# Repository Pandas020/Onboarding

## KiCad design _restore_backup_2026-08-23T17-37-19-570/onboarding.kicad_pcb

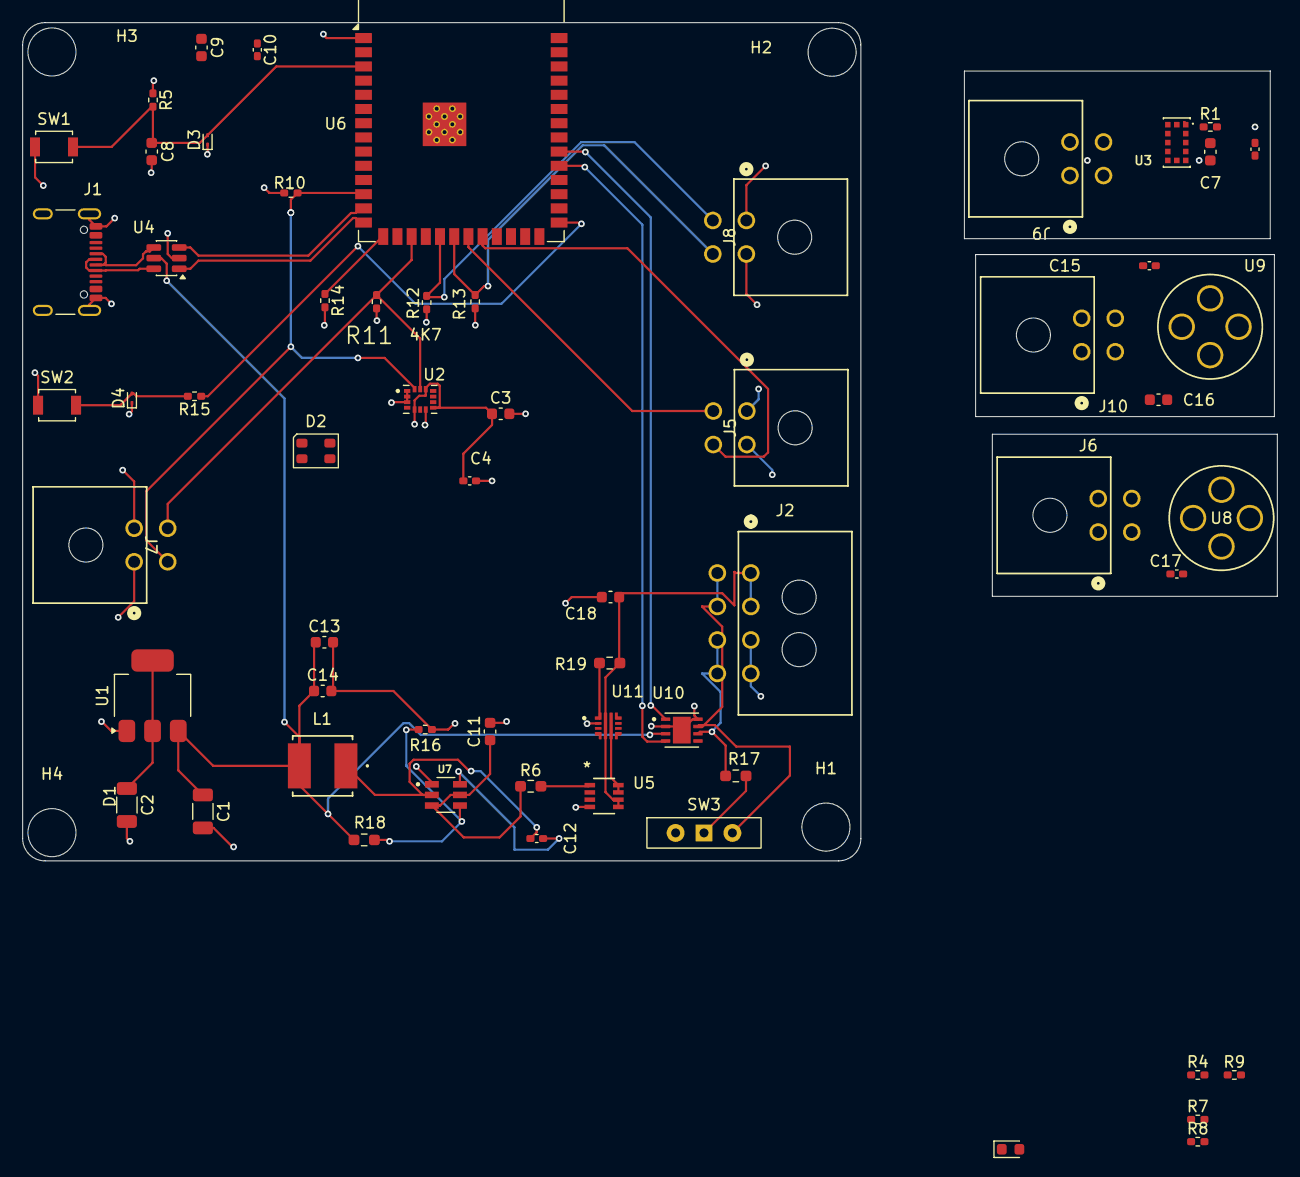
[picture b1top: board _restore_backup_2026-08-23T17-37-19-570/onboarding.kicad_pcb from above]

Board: 4 copper layers, 112.3 x 75.0 mm, 65 parts (0 on the bottom side), 39 nets.

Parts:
C1, C2: 22uF; C_1206_3216Metric
C3: 1uF; C_0603_1608Metric
C4, C5, C10, C12, C15, C17: 100nF; C_0402_1005Metric_Pad0.74x0.62mm_HandSolder
C7, C11: 4U7; C_0603_1608Metric
C8: 1u; C_0603_1608Metric
C9, C13, C14, C16, C18: 10uF; C_0603_1608Metric
D1: RED; LED_0603_1608Metric
D2: CLV1L-FKB; LED_Cree-PLCC4_3.2x2.8mm_CCW
D3, D4: ESD3.3; D_SOD-923
H1, H2, H3, H4: MountingHole; MountingHole_4.3mm_M4
J1: USB_C_Receptacle_USB2.0_16P; USB_C_Receptacle_GCT_USB4105-xx-A_16P_TopMnt_Horizontal
J2: 430450800; CONN_SD-43045-001_08_MOL
J5, J6, J7, J8, J9, J10: 430450400; CONN_SD-43045-001_04_MOL
L1: NRS5030T3R3MMGJ; IND_NRS5030T3R3MMGJ_TAY-M
R1, R5, R15: 10K; R_0402_1005Metric_Pad0.72x0.64mm_HandSolder
R4, R7, R8, R9, R14: 1K; R_0402_1005Metric_Pad0.72x0.64mm_HandSolder
R6, R17: 100R; R_0603_1608Metric_Pad0.98x0.95mm_HandSolder
R10, R11, R12, R13: 4K7; R_0402_1005Metric_Pad0.72x0.64mm_HandSolder
R16: 13K7; R_0402_1005Metric_Pad0.72x0.64mm_HandSolder
R18: 100K; R_0603_1608Metric_Pad0.98x0.95mm_HandSolder
R19: 470K; R_0603_1608Metric_Pad0.98x0.95mm_HandSolder
SW1: RESET; SW_SPST_B3U-1000P
SW2: BOOT; SW_SPST_B3U-1000P
SW3: SW_Wuerth_450301014042; SW_Slide-03_Wuerth-WS-SLTV_10x2.5x6.4_P2.54mm
U1: LM1117DT-3.3; SOT-223-3_TabPin2
U2: ASM330LHHXTR; XDCR_ASM330LHHXTR
U3: VL53L0CXV0DH_1; XDCR_VL53L0CXV0DH_1
U4: USBLC6-2SC6; SOT-23-6
U5: STEF12SAGR; IC8_STEF12SAGR_STM
U6: ESP32-S3-WROOM-1
U7: LMR51420YFDDCR; SOT95P280X110-6N
U8: MLX90614ESF-BCF-000-TU; MLX90614xCF_MEL
U9: MLX90641ESF-BCB-000-TU; MLX90614xCF_MEL
U10: TJA1462ATK_0Z; SON65P300X300X100-9N
U11: LM73100RPWR; IC_LM73100RPWR

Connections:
+3V3: C2.1, C3.1, C4.1, C5.1, C7.1, C9.1, C10.1, C15.1, C16.1, C17.1, D2.1 (A), J5.1, J6.1, J7.1, J8.1, J9.1, J10.1, R1.1, R4.1, R5.1, R10.1, R11.1, R12.1, R13.1, R14.2, U1.2 (VO), U2.5 (VDD_IO), U2.8 (VDD), U2.12 (CS), U3.1 (AVDDVCSEL), U3.1.1 (AVDDVCSEL), U3.11 (AVDD), U6.2 (3V3), U8.3 (VDD), U9.2 (VDD), U10.5 (VIO)
+5V: C1.1, C13.1, C14.1, L1.2, R18.2, U1.3 (VI), U4.5 (VBUS), U10.3 (VCC)
+12V: C11.1, C18.1, J2.1, J2.2, R6.1, R19.2, U5.5 (Source), U5.6 (Source), U7.3 (VIN), U7.5 (EN), U11.5 (IN)
/BRAKE_PWM: J5.4, J6.4, U6.22 (IO14), U8.2 (SDA/PWM)
/BRAKE_SCL: J5.3, J6.3, U6.21 (IO13), U8.1 (SCL/Vz)
/B_RGB: R9.2, U6.35 (IO42)
/CANH: J2.5, J2.6, SW3.3 (A), U10.7 (CANH)
/CANL: J2.7, J2.8, R17.1, U10.6 (CANL)
/D+: J1.A6 (D+), J1.B6 (D+), U4.6 (I/O1)
/D-: J1.A7 (D-), J1.B7 (D-), U4.4 (I/O2)
/ESP_EN: C8.1, D3.2 (A2), R5.2, SW1.2 (B), U6.3 (EN)
/ESP_IO0: R15.1, U6.27 (IO0)
/FDCAN_RX: U6.31 (IO38), U10.4 (RXD)
/FDCAN_TX: U6.32 (IO39), U10.1 (TXD)
/G_RGB: R8.2, U6.34 (IO41)
/IO4: U2.4 (INT1), U6.4 (IO4)
/IO5: U2.9 (INT2), U6.5 (IO5)
/R_RGB: R7.2, U6.33 (IO40)
/SCL: J7.4, J9.4, R11.2, U2.13 (SCL), U3.10 (SCL), U6.17 (IO9)
/SCL2_TTS: J8.3, J10.3, R12.2, U6.19 (IO11), U9.4 (SCL)
/SDA: J7.3, J9.3, R10.2, U2.14 (SDA), U3.9 (SDA), U6.12 (IO8)
/SDA2_TTS: J8.4, J10.4, R13.2, U6.20 (IO12), U9.1 (SDA)
/USB_D+: U4.1 (I/O1), U6.14 (USB_D+)
/USB_D-: U4.3 (I/O2), U6.13 (USB_D-)
GND: C1.2, C2.2, C3.2, C4.2, C5.2, C7.2, C8.2, C9.2, C10.2, C11.2, C13.2, C14.2, C15.2, C16.2, C17.2, C18.2, D1.1 (K), D3.1 (A1), D4.1 (A1), J1.A1 (GND), J1.A12 (GND), J1.B1 (GND), J1.B12 (GND), J1.SH (SHIELD), J2.3, J2.4, J5.2, J6.2, J7.2, J8.2, J9.2, J10.2, R16.1, SW1.1 (A), SW2.1 (A), U1.1 (GND), U2.1 (SDO/SA0), U2.2 (MSDA), U2.3 (MSCL), U2.7 (GND), U3.2 (AVSSVCSEL), U3.3 (GND), U3.4 (GND), U3.6 (GND), U3.12 (GND), U4.2 (GND), U5.4 (GND), U6.1 (GND), U6.40 (GND), U6.41 (GND), U7.1 (GND), U8.4 (VSS), U9.3 (GND), U10.2 (GND), U10.8 (STB), U10.9 (GND), U11.2 (OVLO), U11.8 (GND), U11.9 (IMON)
unnamed: D1.2 (A), R4.2
unnamed: D2.4 (BK), R9.1
unnamed: D2.3 (GK), R8.1
unnamed: D2.2 (RK), R7.1
unnamed: D4.2 (A2), R15.2, SW2.2 (B)
unnamed: R17.2, SW3.1 (B)
unnamed: R1.2, U3.5 (XSHUT)
unnamed: R6.2, U5.1 (ILim)
unnamed: R14.1, U6.15 (IO3)
unnamed: C12.1, U7.6 (CB)
unnamed: R16.2, R18.1, U7.4 (FB)
unnamed: C12.2, L1.1, U7.2 (SW)
unnamed: R19.1, U11.1 (EN/UVLO)
unnamed: U5.7 (Vcc), U5.8 (Vcc), U11.6 (OUT)

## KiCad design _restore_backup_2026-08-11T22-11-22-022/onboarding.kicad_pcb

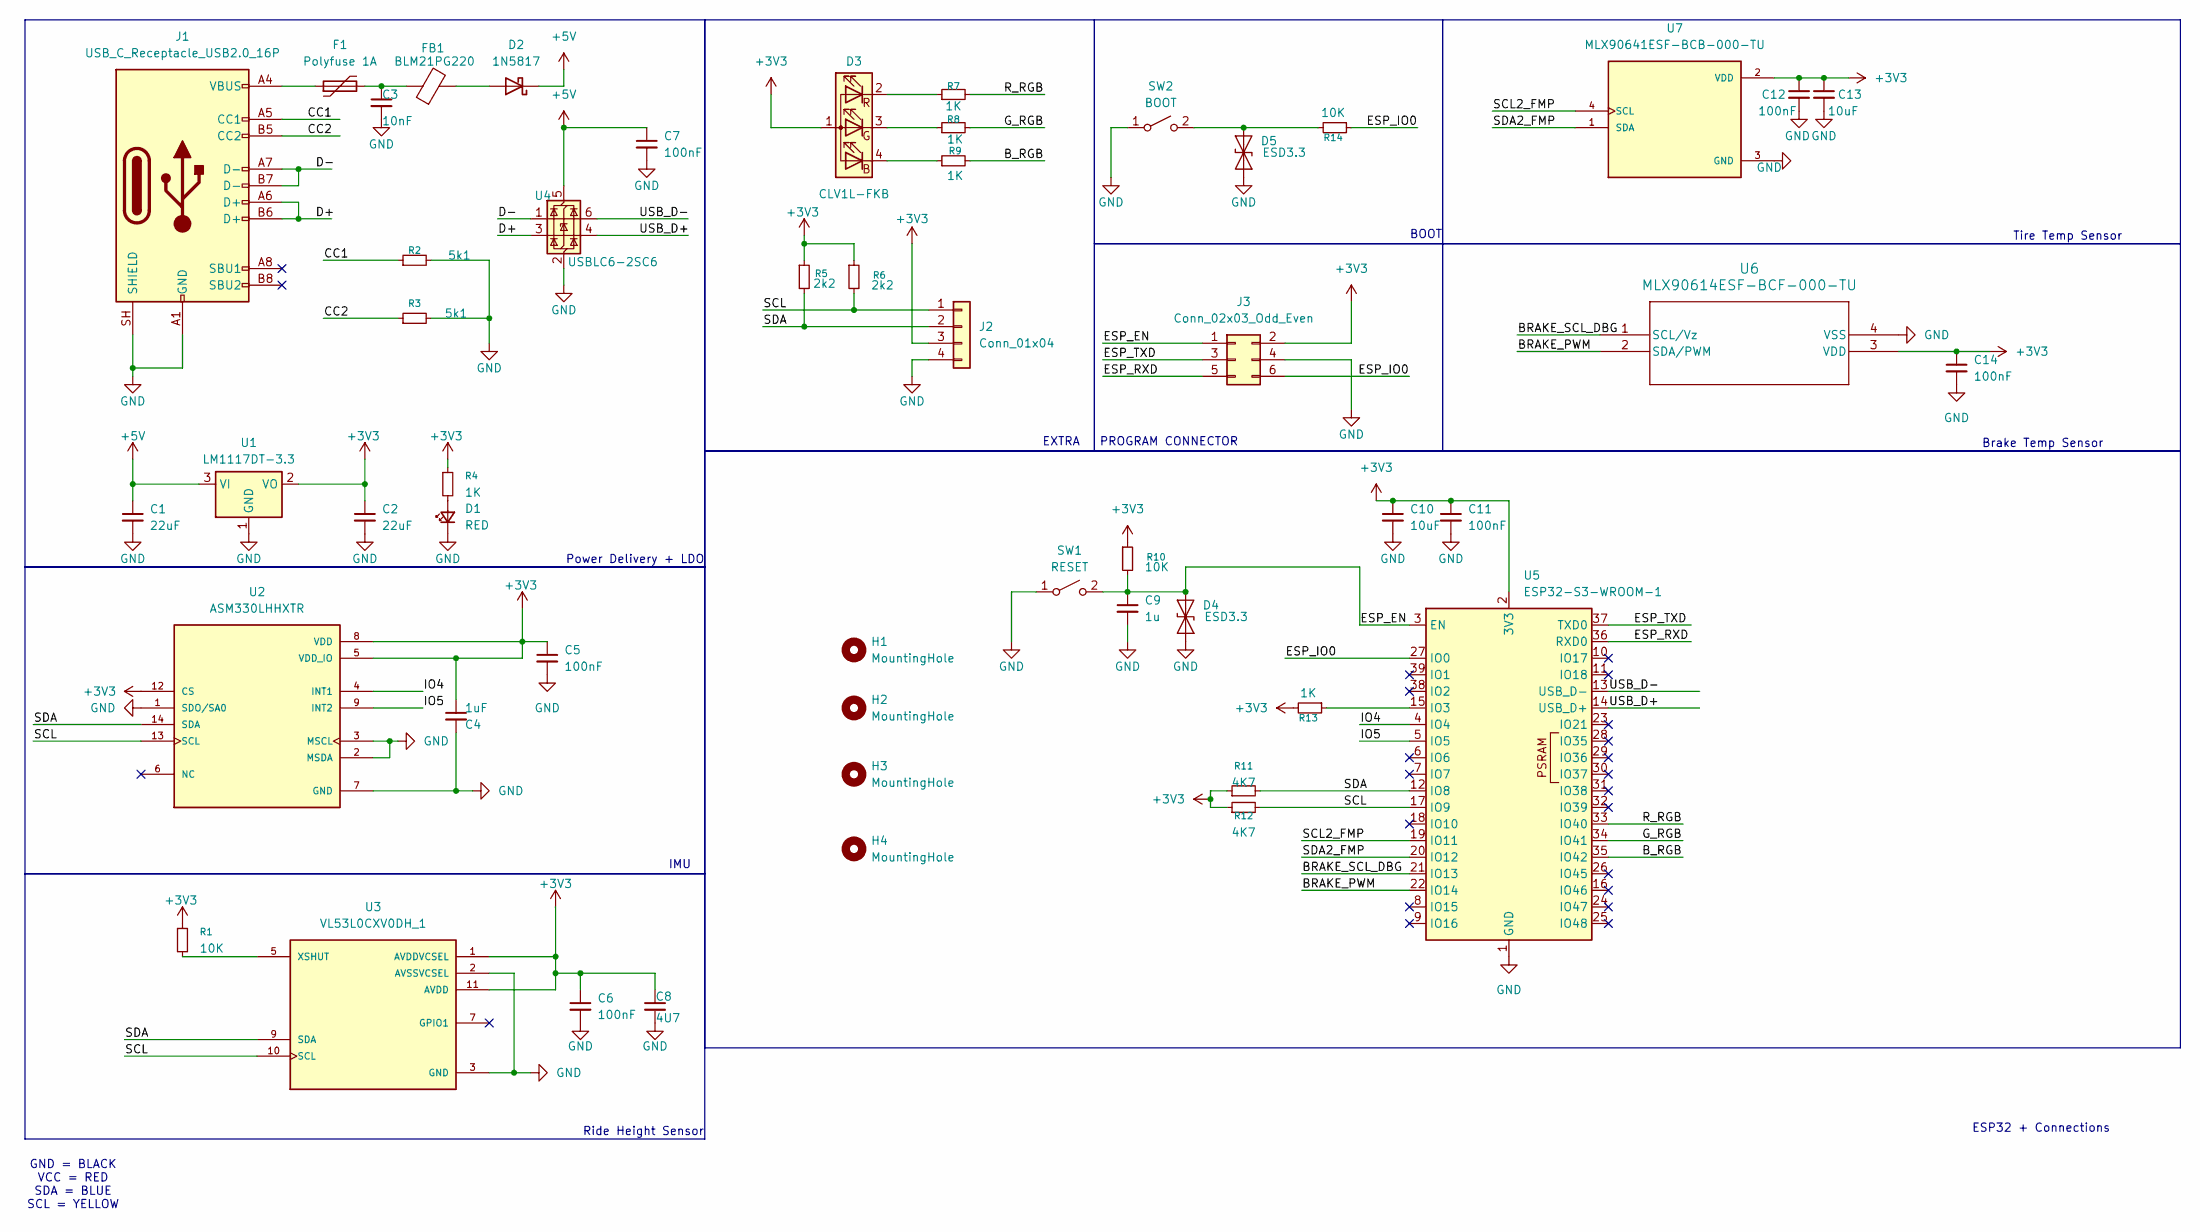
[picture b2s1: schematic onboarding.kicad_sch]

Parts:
C1, C2: 22uF; C_1206_3216Metric
C3: 10nF; C_0402_1005Metric
C4: 1uF; C_0603_1608Metric
C5, C6, C7, C11, C12, C14: 100nF; C_0402_1005Metric_Pad0.74x0.62mm_HandSolder
C8: 4U7; C_0603_1608Metric
C9: 1u; C_0603_1608Metric
C10, C13: 10uF; C_0603_1608Metric
D1: RED; LED_0603_1608Metric
D2: 1N5817; D_SOD-123F
D3: CLV1L-FKB; LED_Cree-PLCC4_3.2x2.8mm_CCW
D4, D5: ESD3.3; D_SOD-923
F1: Polyfuse 1A; Fuse_1206_3216Metric
FB1: BLM21PG220; L_0805_2012Metric
H1, H2, H3, H4: MountingHole; MountingHole_3.2mm_M3
J1: USB_C_Receptacle_USB2.0_16P; USB_C_Receptacle_GCT_USB4105-xx-A_16P_TopMnt_Horizontal
J2: Conn_01x04; JST_SH_SM04B-SRSS-TB_1x04-1MP_P1.00mm_Horizontal
J3: Conn_02x03_Odd_Even; PinHeader_2x03_P2.54mm_Vertical
R1, R10, R14: 10K; R_0402_1005Metric_Pad0.72x0.64mm_HandSolder
R2, R3: 5k1; R_0402_1005Metric_Pad0.72x0.64mm_HandSolder
R4, R7, R8, R9, R13: 1K; R_0402_1005Metric_Pad0.72x0.64mm_HandSolder
R5, R6: 2k2; R_0402_1005Metric_Pad0.72x0.64mm_HandSolder
R11, R12: 4K7; R_0402_1005Metric_Pad0.72x0.64mm_HandSolder
SW1: RESET; SW_SPST_B3U-1000P
SW2: BOOT; SW_SPST_B3U-1000P
U1: LM1117DT-3.3; SOT-223-3_TabPin2
U2: ASM330LHHXTR; XDCR_ASM330LHHXTR; PARTREV 8
U3: VL53L0CXV0DH_1; XDCR_VL53L0CXV0DH_1
U4: USBLC6-2SC6; SOT-23-6
U5: ESP32-S3-WROOM-1
U6: MLX90614ESF-BCF-000-TU; MLX90614xCF_MEL
U7: MLX90641ESF-BCB-000-TU; TO254P912H435-4; PARTREV 11

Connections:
+3V3: C2.1, C4.1, C5.1, C6.1, C8.1, C10.1, C11.1, C12.1, C13.1, C14.1, D3.1 (A), J2.3, J3.2, R1.1, R4.1, R5.1, R6.1, R10.1, R11.1, R12.1, R13.2, U1.2 (VO), U2.5 (VDD_IO), U2.8 (VDD), U2.12 (CS), U3.1 (AVDDVCSEL), U3.1.1 (AVDDVCSEL), U3.11 (AVDD), U5.2 (3V3), U6.3 (VDD), U7.2 (VDD)
+5V: C1.1, C7.1, D2.1 (K), U1.3 (VI), U4.5 (VBUS)
/BRAKE_PWM: U5.22 (IO14), U6.2 (SDA/PWM)
/BRAKE_SCL_DBG: U5.21 (IO13), U6.1 (SCL/Vz)
/B_RGB: R9.2, U5.35 (IO42)
/CC1: J1.A5 (CC1), R2.1
/CC2: J1.B5 (CC2), R3.1
/D+: J1.A6 (D+), J1.B6 (D+), U4.3 (I/O2)
/D-: J1.A7 (D-), J1.B7 (D-), U4.1 (I/O1)
/ESP_EN: C9.1, D4.2 (A2), J3.1, R10.2, SW1.2 (B), U5.3 (EN)
/ESP_IO0: J3.6, R14.1, U5.27 (IO0)
/ESP_RXD: J3.5, U5.36 (RXD0)
/ESP_TXD: J3.3, U5.37 (TXD0)
/G_RGB: R8.2, U5.34 (IO41)
/IO4: U2.4 (INT1), U5.4 (IO4)
/IO5: U2.9 (INT2), U5.5 (IO5)
/R_RGB: R7.2, U5.33 (IO40)
/SCL: J2.1, R6.2, R12.2, U2.13 (SCL), U3.10 (SCL), U5.17 (IO9)
/SCL2_FMP: U5.19 (IO11), U7.4 (SCL)
/SDA: J2.2, R5.2, R11.2, U2.14 (SDA), U3.9 (SDA), U5.12 (IO8)
/SDA2_FMP: U5.20 (IO12), U7.1 (SDA)
/USB_D+: U4.4 (I/O2), U5.14 (USB_D+)
/USB_D-: U4.6 (I/O1), U5.13 (USB_D-)
GND: C1.2, C2.2, C3.2, C4.2, C5.2, C6.2, C7.2, C8.2, C9.2, C10.2, C11.2, C12.2, C13.2, C14.2, D1.1 (K), D4.1 (A1), D5.1 (A1), J1.A1 (GND), J1.A12 (GND), J1.B1 (GND), J1.B12 (GND), J1.SH (SHIELD), J2.4, J3.4, R2.2, R3.2, SW1.1 (A), SW2.1 (A), U1.1 (GND), U2.1 (SDO/SA0), U2.2 (MSDA), U2.3 (MSCL), U2.7 (GND), U3.2 (AVSSVCSEL), U3.3 (GND), U3.4 (GND), U3.6 (GND), U3.12 (GND), U4.2 (GND), U5.1 (GND), U5.40 (GND), U5.41 (GND), U6.4 (VSS), U7.3 (GND)
unnamed: C3.1, F1.2, FB1.1
unnamed: D1.2 (A), R4.2
unnamed: D2.2 (A), FB1.2
unnamed: D3.4 (BK), R9.1
unnamed: D3.3 (GK), R8.1
unnamed: D3.2 (RK), R7.1
unnamed: D5.2 (A2), R14.2, SW2.2 (B)
unnamed: F1.1, J1.A4 (VBUS), J1.A9 (VBUS), J1.B4 (VBUS), J1.B9 (VBUS)
unnamed: R1.2, U3.5 (XSHUT)
unnamed: R13.1, U5.15 (IO3)

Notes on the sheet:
Brake Temp Sensor
PROGRAM CONNECTOR
ESP32 + Connections
Tire Temp Sensor
Power Delivery + LDO
IMU
Ride Height Sensor
BOOT
EXTRA
GND = BLACK VCC = RED SDA = BLUE SCL = YELLOW

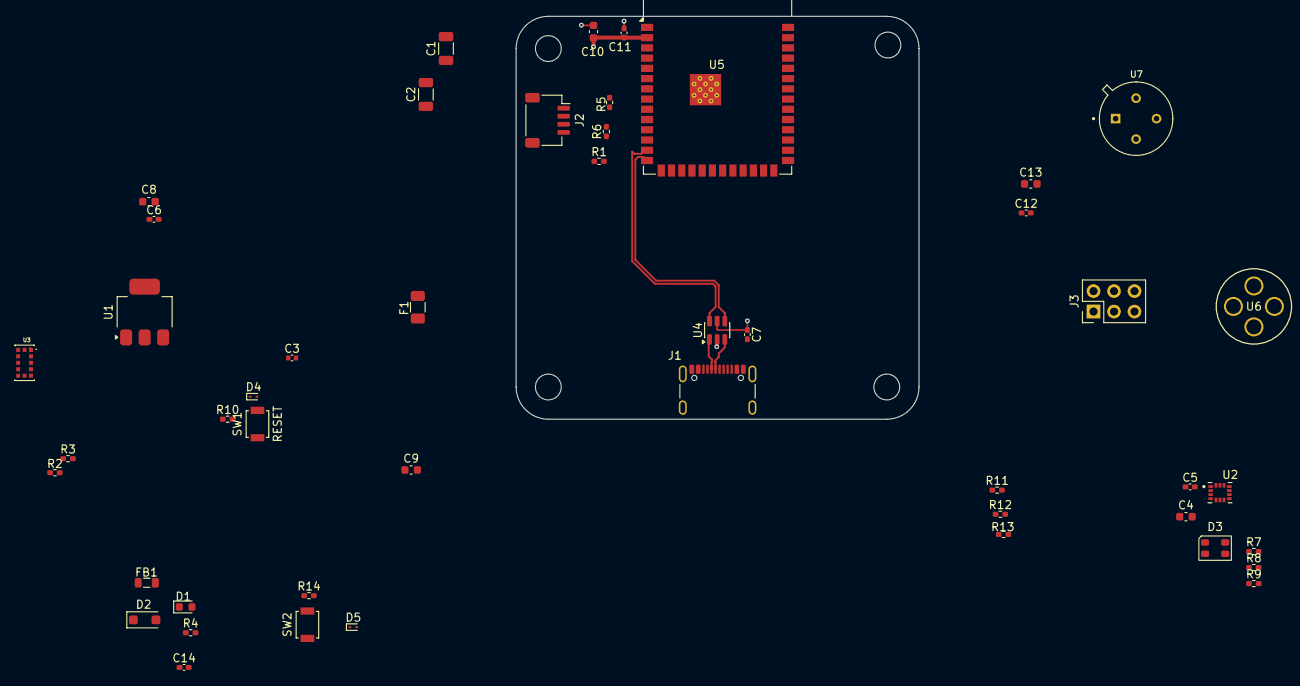
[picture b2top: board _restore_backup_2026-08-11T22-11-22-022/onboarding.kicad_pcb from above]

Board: 4 copper layers, 50.0 x 50.0 mm, 51 parts (0 on the bottom side), 34 nets.
